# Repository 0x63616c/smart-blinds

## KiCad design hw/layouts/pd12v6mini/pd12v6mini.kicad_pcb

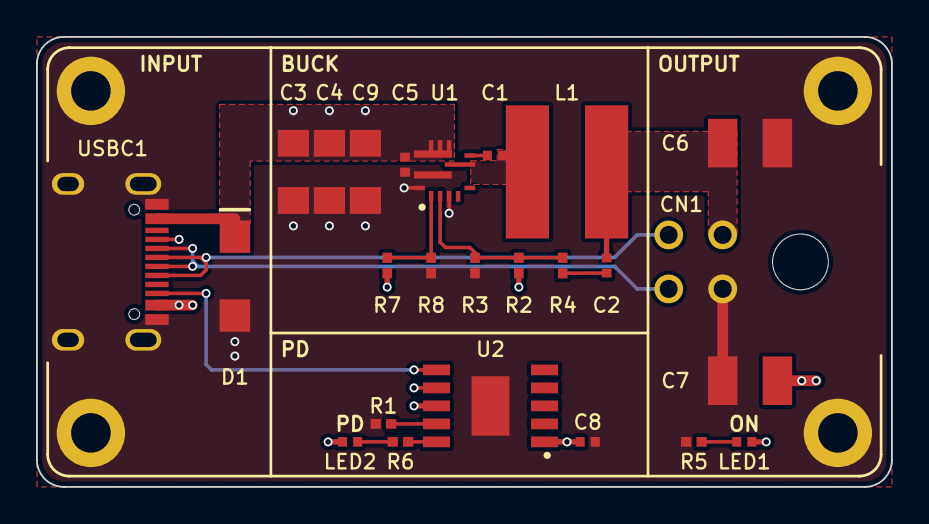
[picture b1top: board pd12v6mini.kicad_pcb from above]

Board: 4 copper layers, 47.5 x 25.0 mm, 29 parts (0 on the bottom side), 16 nets.

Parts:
C1, C2, C5, C8: C0402
C3, C4, C9: C1206
C6, C7: C1210
CN1: CONN-TH_0430450400
D1: SMA_L4.4-W2.6-LS5.0-RD
H1, H2, H3, H4: M2_HOLE
L1: IND-SMD_PSTMAA666460-6R8MB
LED1: LED0402-RD_GREEN
LED2: LED0402-RD
R1, R2, R3, R4, R5, R6, R7, R8: R0402
U1: VQFN-HR-10_L3.0-W3.0_RPA
U2: ESSOP-10_L4.9-W3.9-P1.0-LS6.0-TL-EP
USBC1: USB-C_SMD-TYPE-C-31-M-12_1

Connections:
BOOT: C1.1, U1.7
CC1: U2.7, USBC1.A5
CC2: U2.6, USBC1.B5
CFG1: R1.1, U2.9
EN: R7.2, R8.1, U1.1
FB: R2.2, R3.1, R4.2, U1.2
FF: C2.2, R4.1
GND: C3.2, C4.2, C5.2, C6.2, C7.2, C8.2, C9.2, CN1.2, D1.2, H1.1, H2.1, H3.1, H4.1, R1.2, R3.2, R5.2, R8.2, U1.3, U1.9, U1.10, U2.11, USBC1.1, USBC1.2, USBC1.3, USBC1.4, USBC1.A1B12, USBC1.B1A12
LED_OUT_K: LED1.1, R5.1
LED_PD_K: LED2.1, R6.1
PG_n: R6.2, U2.10
SW: C1.2, L1.1, U1.6
USB_DN: CN1.4, USBC1.A7, USBC1.B7
USB_DP: CN1.3, USBC1.A6, USBC1.B6
VBUS: C3.1, C4.1, C5.1, C8.1, C9.1, D1.1, LED2.2, R7.1, U1.8, U2.1, U2.8, USBC1.A4B9, USBC1.B4A9
VOUT: C2.1, C6.1, C7.1, CN1.1, L1.2, LED1.2, R2.1

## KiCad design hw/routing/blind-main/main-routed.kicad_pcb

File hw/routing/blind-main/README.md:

# Historical 196-part main-controller routing

This directory is the **historical 196-part routing checkpoint**, not the current
54 × 80 mm controller. Its source, geometry, manifests and validation results
belong together at [commit ea7bab1566812b4611e3c1e800e67b5ede44651c](https://github.com/0x63616c/smart-blinds/tree/ea7bab1566812b4611e3c1e800e67b5ede44651c).
That commit contains the exact source capture SHA
`2ef8c8d6168420d0de25bb6a4c4b3d778d73c1fd55e97ca068adafe70fbeadd7`
recorded in `route-record.json`. Reproduce its checks from that revision through
the isolated Linux runner. Do not point those checks at the newer 206-part
capture or present the historical findings as current-board validation.

This was a partial four-layer routing study, not a manufacturing release.
The derivative retains the 54 × 68.5 mm outline with its USB tab, all 196
footprints, 609 physical pin identities, 139 net partitions, 17 mechanical/thermal
anchors and 13 RF, connector-foot and clamp reservations.

The checkpoint contains 1013 segments and 255 vias. It routes the local charger
switching/bypass network, motor-driver fly/pump/VM and output paths, regulator
bypass/output/sense paths, and a 3.3 V feed to the radio module. In1 remains a
continuous filled ground-return island; no signal traces use that layer. The
module power feed uses In2 beneath the permitted module body, with vias outside
its solder lands and unchanged antenna keepouts.

Actual KiCad 10 DRC reports **122 unconnected items**. No short, copper/edge/hole
clearance, track-width, courtyard-overlap, keepout, mask-bridge or dangling-route
failure is accepted. The report retains 258 silkscreen/text findings, four
library-footprint differences and five footprint-type findings. The latter
include mixed through-hole/thermal features and incorrectly classified library
attributes; they require footprint/assembly review, not a blanket waiver.
Three unrelated default-disabled DRC categories are listed in `checks.json`.

`checks.py` independently checks actual pad shapes, masks/paste settings, net
partitions, layer/rotation/placement, outline, keepouts, courtyard bounds and
encoder-wire height clearance. It also follows physical copper shapes through
70 required connection groups, including the ground fill. A matching net name
alone cannot pass. Twenty-six earlier injected faults are rejected: moved USB connector, changed motor pad,
weakened RF reservation, cut module supply, removed return plane, cut charger
bypass return, cut PD bypass, cut USB input, removed quiet return via, and an
extra connection from the quiet return to the input-capacitor return, plus open
PD enable, UV divider, raw discharge and address-ground branches. The new controls
also cut the charger input, PMID and SYS bulk branches and input-capacitor return,
and place a same-net solder land over an ordinary open via. All 38 new distribution
vias preserve at least 0.20 mm from their drill edges to top solder lands; native
same-net clearance alone does not check this assembly condition. Both REGN and VBUS bypass
returns have two nearby ground vias, as required by the charger layout guide.
The checks remove the plane from the local graph before counting those vias. The generator is deterministic across repeated local runs.

The USB addition connects both VBUS contacts to the eFuse and its output
reservoir, with local input capacitance and a shunt TVS. It also connects the PD
supply diode and three separate bypass branches, and both CC/protection/dead-battery paths. The two MCU data resistors
have short local stubs; the completed data paths are described below. The eFuse's
current-setting, slew and divider-endpoint components return through an isolated
same-face branch to one ground via. An independent plane-free copper check
requires exactly those five quiet-ground pads and that one via; it rejects the
input-capacitor return joining this branch even though the net names agree.

The PNP enable stage, both voltage dividers, raw/output discharge chains and
PD address/reset/bus resistor branches are now connected. Their explicit
coordinates are replayed from `usb-control-routes.json`; reproduction performs
no route search. Five separate local ground vias serve the address and factory
bus resistors without joining the eFuse quiet-ground branch.

Factory access pads remain open; the USB data pair now reaches the module.
The completed control connections do not establish negotiated startup or
detach/discharge timing; the PD configuration and electrical tests remain
required. The 0.3 mm central-pad escapes and 0.8 mm back-layer power trunks
need current/temperature review; the present geometry is not a current rating.
The input TVS's specified pulse clamp can exceed downstream DC limits; placement
does not resolve that separate transient qualification issue. The eFuse layout
uses a quiet return, but loop impedance and coupling still need review.

The eFuse output now reaches the charger VBUS pins and input capacitors. The four
PMID and five SYS bulk capacitors connect to their existing local fast-bypass
branches through explicit two-via fanouts and In2 distribution traces. Input and
bulk-capacitor grounds join the uninterrupted In1 return. The replay coordinates
in `charger-power-banks.json` and `distribution.py` require no routing search.
The previous 581 copper items are retained. Fifteen previously unwired parts move
to make room, including the encoder supply block; all mechanical anchors remain.
These distributed reservoirs still need ripple-current, return-loop and thermal
review. The 0.6–0.8 mm In2 traces use 15.2 µm copper, so geometric clearance is not
a demonstrated continuous-current rating. Pack feed and onward SYS distribution
remain open.

The next extension connects both VAC inputs, BATP feedback, TS and ILIM networks,
PROG and their local returns. Six previously unwired control parts move; no
mechanical anchor changes. Its explicit paths in `charger-control-routes.json`
are replayed by `charger_controls.py`. A bootstrap via moves 0.25 mm to provide
two adjacent sensing escapes; its two incident traces follow it. The other 696
previous copper items are retained exactly. Seventeen control-area vias
(sixteen added and that relocated via) pass the same 0.20 mm drill-to-solder-land
margin, including same-net lands. Five new deliberate opens and a same-net
control-via intrusion are rejected. These connections need switch-noise,
feedback accuracy, thermal and transient review; full charger control, bus and
charge-permission wiring remain unfinished.

A subsequent assembly-clearance pass moves twelve ordinary vias by at most
0.35 mm and adjusts their sixteen incident traces. Five short top-layer stubs
preserve connections that previously relied on via copper touching a solder
land. No component moves. That earlier stage checked 178 routed vias. The clamp, USB and local supervision stages extend this to all 255 via drills, which remain at least 0.20 mm
from every top solder land, including lands on the same net; the ordinary
KiCad same-net clearance check alone does not ensure this. A deliberate
same-net intrusion at the USB input capacitor is rejected. The explicit
`via-land-clearance.json` changes replay through `via_lands.py`; this is not a
filled/capped via-in-pad process. Thermal holes inside library footprints still
require their separate solder/paste and assembly-process review.

The regenerative clamp now connects its eight-resistor bank, two series power
MOSFETs, detector/divider/feedback, local supply and bypasses, thermostat and latch.
Its 19 local multi-pad nets and eight load-path groups are checked using physical
copper, including every duplicate pad. Three separate plane-free return checks
keep the load, quiet detector and LDO bypass returns distinct before their plane
entries. Eight additional injected faults reject opens and an incorrect shared
return. All 34 old/new fault controls pass. The external `thermal_ok` and `G`
connections to the main inhibit and fault indication remain open.

`regen.py` consumes the preceding pipeline stage and replays finite geometry from
`regen-routes.json`; it does not embed a completed baseline or run a route search.
It replaces twelve exact low-current segments and one redundant NTC via, retains
all other incoming copper, and adds 249 items. Twenty-five previously unwired
clamp components move relative to the preceding published checkpoint. The eight
resistor and all mechanical anchors stay fixed. A now-obsolete NTC via is
explicitly required absent; the other sixteen control-area vias remain checked.

The selected 38.199 mm × 1.2 mm back-layer feed replaces an evaluated
48.804 mm × 0.8 mm detour. Nominal 35 µm-copper estimates at 20 °C are 15.68 mΩ
versus 30.05 mΩ, excluding vias, temperature and process variation. The actual
filled In1 plane contains a complete 1.2 mm swept-width, 39.802 mm return witness;
this is checked by polygon subtraction. It is not an ampacity or current-distribution
result. In1 is only 15.2 µm thick, and the eight 2 W resistor labels do not establish
16 W continuous capability for this compact assembly.

The shorter power loop requires three reviewed signal changes: PROG grows from
17.771 to 28.509 mm on B.Cu; NTC grows from 5.768 to 12.980 mm on B/F; the SW1 bootstrap
return shrinks from 8.087 to 4.175 mm. `regen_analog.py` reports their actual copper
neighbors and proves an intervening filled In1 shield at the NTC's projected
crossings with the B.Cu feed. The closest NTC segment remains only 0.205 mm from
the motor bulk PACK solder land; PROG remains a long startup-sampled branch.
These are explicit noise/layout qualification limits. A bounded 0.2 mm-grid search
for a closer one-part PROG relocation found no accepted closer position while
other parts/copper were fixed; it does not rule out a wider repack.

Comparator overshoot, FET SOA, pulse repetition, thermostat-to-resistor coupling,
printed-case/battery temperature and real motor regeneration remain untested.
An opened thermal cutoff cannot absorb sustained manual back-drive.

The complete placement change list is in `checks.json`. Many support components
have moved from the first placement to make local electrical loops possible.
The critical-loop review remains incomplete: especially charger bootstrap
routing, current/return geometry, switch-node coupling and module supply
impedance. The external 100 nF and bulk radio capacitors are about 18 mm from
the module supply pin; the wide internal feed is a layout candidate, not
proof of adequate local decoupling. Geometric clearance does not establish
electrical performance.

The USB data extension connects both reversible contact pairs through the moved
TPD2E2U06 and the existing module-side 22 Ω resistors. The ESD package moves to
local (22.8, 1.7), 180°; only its three old ground branches/two vias and three CC1
segments are replaced. `usb_data.py` consumes the current clamp output and
replays `usb-data-routes.json`. The base placement remains in `placement.json`;
that data file contains the explicit final ESD override. All other incoming
copper and the circuit graph remain unchanged, including after filling/saving.

Both long front traces have continuous direct In1 reference. A local In2 ground
zone references the short back crossover. The saved fill is checked for overlap
with each signal via, and missing reference is accepted only within D-minus's
own necessary via openings, with the project's 5 µm polygon-arc tolerance plus
0.5 µm audit tolerance. A prior saved merge had stale filled polygons; the
maintained stage now rebuilds and persists them. The neighboring D-plus segment
no longer clips D-minus's antipad. One short ESD pin-4 return reaches one local
via; optional NC pins 1/2 are grounded as TI permits.

The actual track-centerline graph gives approximately 88.235 mm from each A-side
contact to its series resistor and 89.235 mm from each B-side contact. It also
checks that each shortest path passes through its protection pad, and removing
that pad node must disconnect every connector-to-resistor centerline path. D-minus uses
two active through-layer transitions; D-plus uses none. Planar length equality
is **not** electrical-delay equality or a 90 Ω impedance result. One localized
D-plus fold at v23–24.8 replaces the earlier two-fold study and adds about
6.264 mm; the longer perimeter is parallel. The fold temporarily widens the pair
spacing, and the connector-side protection lead remains a layout tradeoff.
These need stackup/return-field/ESD review and actual full-speed USB tests.

Six new fault controls cut a D-plus branch, one D-minus reversible contact,
the ESD return, the back reference, and restore stale ground within a signal
antipad, and add a longer parallel path that bypasses the ESD pad.
All 40 controls through the USB stage pass; the later supervision stage brings the total to 47. The physical USB data connections are
complete; USB performance and manufacturing acceptance remain unfinished.

## Rules and outstanding work

The study retains the preliminary 1.6 mm JLC3313 four-layer descriptor: 35 µm
outer and 15.2 µm inner copper. Comparative minima are 0.15 mm trace/clearance,
0.20 mm copper-to-edge and hole-to-copper, 0.25 mm hole-to-hole, 0.20 mm minimum
hole and 0.10 mm annular ring. Ordinary route vias are 0.6/0.3 mm; selected
fine-pitch escapes use 0.5/0.25 mm. Existing thermal holes require their own
mask/paste/assembly-process review. These rules are not a current rating,
impedance approval, assembly quote or final fabrication profile.

Still unfinished: USB factory access and impedance/ESD qualification, pack feed and onward SYS
current distribution, clamp external inhibit/fault connections and onward supervisor buses, complete signal
routing, thermal and transient review, sparse silkscreen, final ERC/DRC and a
manufacturing quote. No autorouter result substitutes for the local power-layout review.

The [local supervision stage](local-supervision.md) adds 59 checked branches and
seven injected faults to the protected USB checkpoint. All 47 fault controls pass.
It preserves the incoming copper and moves fourteen previously unwired small
parts. The local encoder returns meet at the regulator GND land, checked by
physically cutting that land from the graph. Longer bypass/pull-up paths and the
unfinished ADC connection remain explicit layout limitations.

The [monitored-PD revision](../../../docs/electrical/monitored-pd-revision.md)
removes the obsolete VSYS-ground branch and two factory bus pull-downs from the
maintained stages. It preserves all1268 surviving copper items and all194 common
footprint placements. The two new parts are staged but unrouted; shared SDA/SCL,
ALERT and the new VSYS bypass still need physical routing. All47 existing fault
controls pass against the revised graph. No new feeder SKU is introduced.

## Reproduce

Use KiCad 10 and its distribution Python bindings, from the repository root:

```sh
xvfb-run -a /usr/bin/python3 hw/routing/blind-main/route.py
xvfb-run -a /usr/bin/python3 hw/routing/blind-main/checks.py --negative-tests
```

On macOS use KiCad's bundled Python, without `xvfb-run`. Intermediate files stay
under `work/main-route-build/`. The checked-in project template is used; no
untracked local KiCad project or global rule override is required. Never pass
this routed derivative through the unrouted-only atopile normalizer.

Layout references: [BQ25798, §8.4](https://www.ti.com/lit/ds/symlink/bq25798.pdf),
[DRV8874, §10](https://www.ti.com/lit/ds/symlink/drv8874.pdf),
[TPS62902, §8.5](https://www.ti.com/lit/ds/symlink/tps62902.pdf),
[Espressif layout guidance](https://docs.espressif.com/projects/esp-hardware-design-guidelines/en/latest/esp32c6/pcb-layout-design.html),
[official DevKit layout](https://dl.espressif.com/dl/schematics/esp32-c6-devkitc-1-pcb-layout_v1.2.pdf),
[STUSB4500](https://www.st.com/resource/en/datasheet/stusb4500.pdf),
[TPS25947, §8.4](https://www.ti.com/lit/ds/symlink/tps25947.pdf),
[TLV6710, §11](https://www.ti.com/lit/ds/symlink/tlv6710.pdf),
[TPS709, §10.1](https://www.ti.com/lit/ds/symlink/tps709.pdf),
[TMP302](https://www.ti.com/lit/ds/symlink/tmp302.pdf),
[JLC capabilities](https://jlcpcb.com/capabilities/pcb-capabilities), and
[JLC stackups](https://cart.jlcpcb.com/client/template/placeOrder/impedance.html).
These guide the study; they do not validate the finished board.

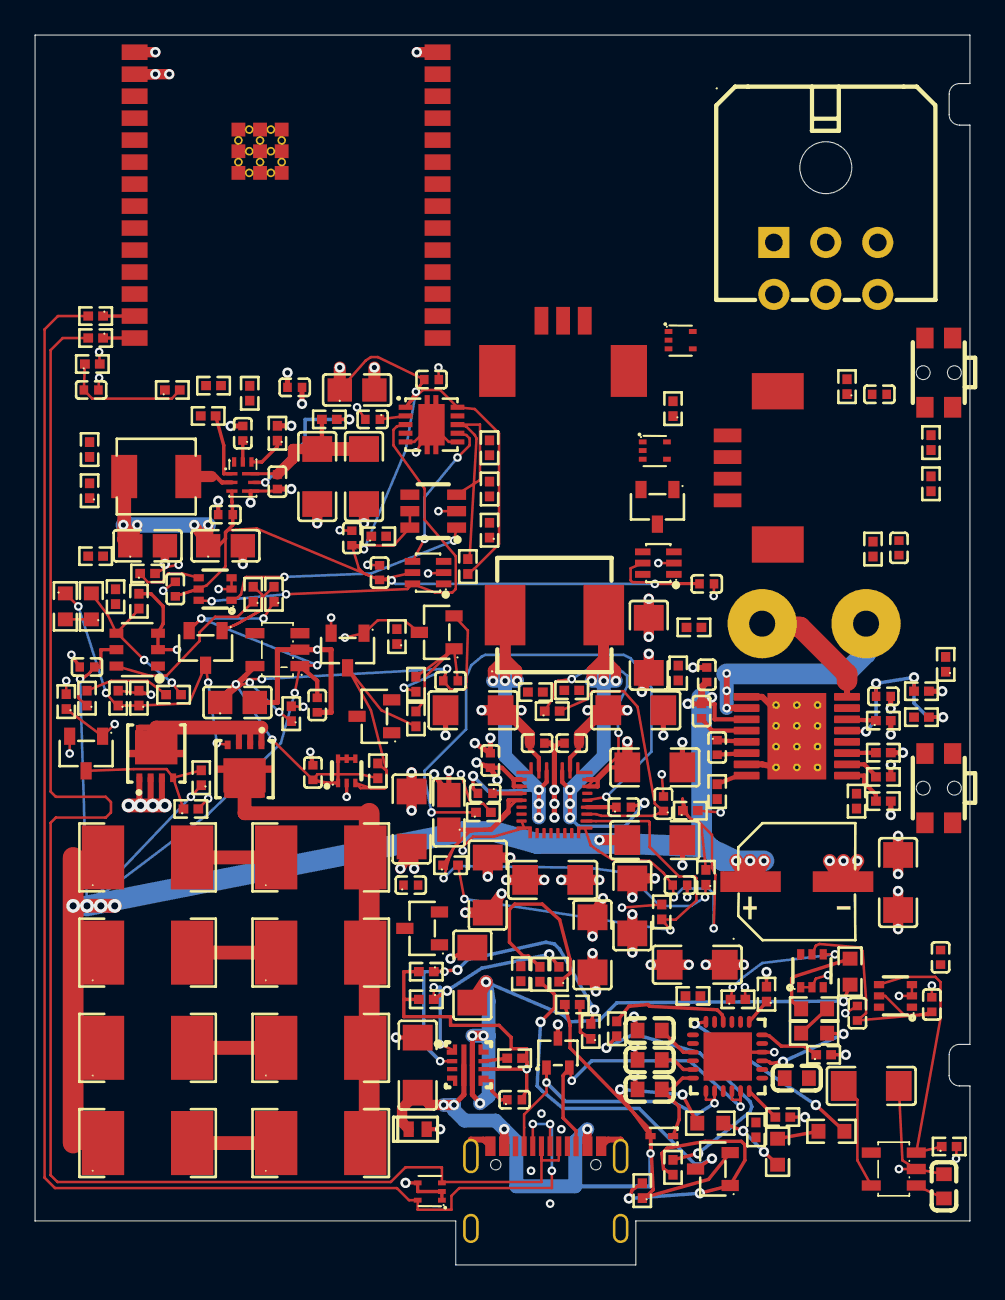
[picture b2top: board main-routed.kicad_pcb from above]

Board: 4 copper layers, 54.0 x 71.0 mm, 196 parts (0 on the bottom side), 110 nets.

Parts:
C1, C2, C6, C7, C9, C10, C11, C12, C16, C17, C18, C19, C20, C40, C42, C49, C54: C1206
C3, C4, C5, C8, C13, C15, C21, C22, C23, C24, C26, C27, C28, C29, C30, C32, C33, C34, C35, C36, C37, C38, C41, C45, C46, C50, C52, C55, C56, C57, C58, C59, C60: C0402
C14, C25, C39, C43, C44: C0805
C31: CAP-SMD_BD6.3-L6.6-W6.6-LS7.3-FD
C47, C48, C51, C53, C61: C0603
D1, D2, D6: SOT-553-5_L1.6-W1.2-P0.50-LS1.6-TL-1
D3: SOD-523_L1.2-W0.8-LS1.6-RD
D4: SOT-323-3_L2.1-W1.3-P1.32-LS2.1-BR
D5: DFN1610-2_L1.6-W1.0-P1.05-RD
J1: CONN-TH_43045-0600
J2: CONN-SMD_4P-P1.25_53261-0471
J3: CONN-TH_532610371
L1: IND-SMD_L7.2-W6.6_GPSR07X0
L2: IND-SMD_L4.4-W4.2
Q1, Q2, Q3, Q4, Q5, Q7, Q8, Q10: SOT-23-3_L2.9-W1.3-P1.90-LS2.4-BR
Q6, Q9: PDFN-8_L3.3-W3.3-P0.65-BL
R1, R2, R3, R4, R5, R6, R7, R8, R9, R10, R11, R12, R13, R14, R15, R16, R17, R18, R19, R20, R21, R22, R23, R24, R25, R26, R27, R28, R29, R30, R31, R32, R33, R34, R35, R36, R37, R38, R39, R40, R41, R44, R45, R46, R47, R48, R49, R50, R51, R52, R56, R57, R58, R62, R63, R65, R66, R67, R68, R77, R78, R79, R80, R81, R82, R83, R84, R85, R86, R87, R88, R89, R90, R91, R92, R93: R0402
R42, R43, R69, R70, R71, R72, R73, R74: R2512
R53, R54, R55, R59, R60, R61, R75, R76: R0603
SW1, SW2: SW-SMD_4P-L3.5-W3.0-P1.6-LS4.6
TP1, TP2: WirePad18
U1: QFN-29_L4.0-W4.0-P0.40-TL-BQ25792RQMR
U2, U14: SOT-363_L2.0-W1.3-P0.65-LS2.1-BR
U3: WIRELM-SMD_ESP32-C6-WROOM-1
U4: HTSSOP-16_L5.0-W4.4-P0.65-LS6.4-BL-EP
U5: TSOT-23-6_L2.9-W1.6-P0.95-LS2.8-BR
U6, U13: SOT-23-5_L3.0-W1.7-P0.95-LS2.8-BR
U7: SOT-5X3-6_W1.6-L1.2-P0.50-LS1.6-BL
U8, U12, U17: SC-70-6_L2.0-W1.3-P0.65-LS2.1-BR
U9: VQFN-HR-9_L2.0-W1.5-P0.50-TL
U10: VQFN-10_L2.0-W2.0-P0.45-TL
U11: QFN-24_L4.0-W4.0-P0.50-BL-EP2.8
U15: SOT-23-6_L2.9-W1.6-P0.95-LS2.8-BR
U16: VSON-10_L3.0-W3.0-P0.50-TL-EP
USBC1: HRO_TYPE_C_31_M_12

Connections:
1: C4.1, U1.4
2: C5.2, L1.2, U1.26
4: U2.4, U3.7
6: U2.6, U3.6
10: R29.2, U3.10
ALERT: R63.2, U1.21, U3.24, U11.19
BATP: C3.1, R1.2, U1.18
C: Q3.3, R66.1
CC2: D4.2, U11.4, U11.5, USBC1.B5
CE_n: Q1.3, R2.2, U1.13
CPH: C32.1, U4.13
CPL: C32.2, U4.14
CWD: C59.1, U16.2
D: Q10.3, R32.2, U3.19, U4.4
DISCH: R55.2, U11.9
DVDT: C50.1, U10.7
EN: R68.1, U12.4, U13.3
G: Q4.1, Q7.1, Q8.3, Q10.1, R88.1
ILIM_HIZ: R4.1, R5.2, U1.17
ILM: R52.1, U10.9
MODE_S_CONF: R45.1, U9.7
MR: R93.2, U15.3, U16.8
OUTB: R40.1, U5.6
PG: R46.2, U9.1
PMODE: R35.2, U4.16
PROG: R8.1, U1.20
RESET: R62.1, U11.6
SCL: J1.4, R27.2, U1.14, U3.12, U11.7
SDA: J1.3, R28.2, U1.15, U3.11, U11.8
SDRV: C15.1, U1.24
SS_TR: C46.1, U9.8
SW: L2.1, U9.2
VBUS_EN_SNK: R50.2, U11.16
VBUS_VS_DISCH: R61.2, U11.18
VCP: C33.1, U4.12
WDI: U14.4, U16.7
Y: R38.1, R39.1, U4.3, U17.4
allow_n-line: R24.2, U3.21, U12.6
boot_n: R19.2, U3.15
c_1v2-1: C47.1, U11.21
c_2v7-1: C48.1, U11.23
c_adc-1: C24.1, R14.2, R15.1, U3.27
c_boot1-1: C4.2, L1.1, U1.28
c_boot2-1: C5.1, U1.19
c_down-1: C27.1, R22.2, SW1.1, SW1.2, U3.9
c_hot_filter-1: C37.1, C39.1, C55.1, Q8.2, R80.1, R81.1, R83.1, U6.5, U7.1, U7.4, U7.5, U7.6
c_pmid1-1: C9.1, C10.1, C11.1, C12.1, C13.1, U1.29
c_ref-1: C34.1, R36.2, R37.1, U4.5
c_regn-1: C14.1, R2.1, R5.1, R10.1, U1.5
c_up-1: C30.1, R30.2, SW2.1, SW2.2, U3.8
c_vdd-1: C51.1, D3.1, U11.24
channel_a: D1.3, J2.3, R12.1, R13.2
channel_b: D1.5, J2.4, R17.1, R18.2
charger-1: Q1.1, Q2.3, R3.1
charger-1-1: Q2.1, R6.2, R7.1
connector-1: D4.1, U11.1, U11.2, USBC1.A5
controller-1: R11.1, R12.2, U2.1
controller-1-1: R16.1, R17.2, U2.3
controller-1-2: R21.1, U3.13
controller-1-3: R23.1, U3.14
controller-2: C29.1, R25.2, R26.2, U3.26
current_raw: R14.1, R31.1, U4.6
efuse-1: R65.1, R67.2, U10.1
encoder-output-hv: C54.1, J2.2, R13.1, R18.1, U13.5
heartbeat-line: R92.2, U3.25, U14.3
home_contact_n: D6.3, D6.5, J3.3, R25.1
host_logic-hv: C23.1, C25.1, C26.1, C28.1, C43.1, C44.1, C45.1, C52.1, C56.1, C57.1, C58.1, C60.1, C61.1, L2.2, Q2.2, R7.2, R19.1, R20.1, R22.1, R24.1, R26.1, R27.1, R28.1, R29.1, R30.1, R32.1, R35.1, R36.1, R46.1, R63.1, R89.1, R90.1, R92.1, R93.1, U2.5, U3.2, U8.5, U9.3, U11.22, U12.5, U14.5, U15.5, U15.6, U16.1, U16.10, U17.5
hv: C1.1, C2.1, C31.1, C33.2, C35.1, C36.1, C38.1, J1.1, Q5.2, R1.1, R41.1, R42.1, R69.1, R71.1, R73.1, R84.1, R86.1, U1.22, U1.23, U4.11, U5.5, U6.1
in1-1: R33.1, U3.16, U4.1
in2-line: R34.1, U3.17, U4.2
line: R6.1, R20.2, U3.20
logic_supply-EN: R44.2, U9.5
lv: C1.2, C2.2, C3.2, C6.2, C7.2, C8.2, C9.2, C10.2, C11.2, C12.2, C13.2, C14.2, C15.2, C16.2, C17.2, C18.2, C19.2, C20.2, C21.2, C22.2, C23.2, C24.2, C25.2, C26.2, C27.2, C28.2, C29.2, C30.2, C31.2, C34.2, C35.2, C36.2, C38.2, C39.2, C40.2, C41.2, C42.2, C43.2, C44.2, C45.2, C46.2, C47.2, C48.2, C49.2, C50.2, C51.2, C52.2, C53.2, C54.2, C55.2, C56.2, C57.2, C58.2, C59.2, C60.2, C61.2, D1.1, D1.2, D1.4, D2.1, D2.2, D2.4, D4.3, D5.2, D6.1, D6.2, D6.4, J1.2, J1.6, J2.1, J3.1, Q1.2, Q4.2, Q7.2, Q9.1, Q9.2, Q9.3, Q10.2, R3.2, R4.2, R8.2, R9.2, R11.2, R15.2, R16.2, R31.2, R33.2, R34.2, R37.2, R38.2, R39.2, R45.2, R47.2, R48.2, R52.2, R56.2, R62.2, R65.2, R68.2, R77.2, R78.2, R81.2, R82.2, R85.2, R88.2, R91.2, SW1.3, SW1.4, SW2.3, SW2.4, U1.10, U1.11, U1.27, U2.2, U3.1, U3.28, U3.29, U3.30, U3.31, U3.32, U3.33, U3.34, U3.35, U3.36, U3.37, U4.9, U4.15, U4.17, U5.2, U5.3, U6.2, U7.2, U8.2, U8.3, U9.4, U10.8, U11.10, U11.25, U12.2, U12.3, U13.2, U14.2, U15.2, U16.5, U16.6, U16.11, U17.1, U17.2, USBC1.1, USBC1.2, USBC1.3, USBC1.4, USBC1.A1B12, USBC1.B1A12
motor_a: TP1.1, U4.8
motor_b: TP2.1, U4.10
motor_request_n-line: R89.2, U3.18, U14.1
motor_sleep_n-Y: R91.1, U8.4, U17.3
pack_ntc: C22.1, J1.5, R9.1, R10.2, U1.16
pd-1: R47.1, U11.12
pd-1-1: R48.1, U11.13
q_drive-1: Q5.3, Q6.4, R75.1, R77.1, R78.1
q_enable-1: Q3.1, R49.1, R51.2
r_base1-1: R49.2, R50.1
r_dump1a-1: R42.2, R43.1
r_dump2a-1: R69.2, R70.1
r_dump3a-1: R71.2, R72.1
r_dump4a-1: R73.2, R74.1
r_feedback1-1: R75.2, R76.1
r_out_dis1-1: R53.2, R54.1
r_out_dis2-1: R54.2, R55.1
r_ov_top1-1: R57.2, R58.1
r_raw_dis1-1: R59.2, R60.1
r_raw_dis2-1: R60.2, R61.1
r_threshold_top1-1: R86.2, R87.1
r_uv_top1-1: R66.2, R67.1
raw-hv: C49.1, D3.2, D5.1, Q3.2, R51.1, R57.1, R59.1, U10.5, USBC1.A4B9, USBC1.B4A9
regen-2: C37.2, Q8.1, R79.2, R80.2
regen-2-1: Q6.5, Q6.6, Q6.7, Q6.8, Q6.9, R43.2, R70.2, R72.2, R74.2
regen-2-2: Q5.1, R40.2, R41.2
reset_n: R90.2, U3.3, U8.1, U12.1, U15.1
series_mid: Q6.1, Q6.2, Q6.3, Q9.5, Q9.6, Q9.7, Q9.8, Q9.9
source-hv: C16.1, C17.1, C18.1, C19.1, C20.1, C21.1, C40.1, C41.1, C42.1, C53.1, R44.1, U1.25, U9.6, U13.1
supervision-6: U8.6, U14.6, U16.3
thermal_gate: Q4.3, Q9.4, R82.1, R84.2
thermal_ok: Q7.3, R79.1, R83.2, U7.3, U17.6
threshold: R76.2, R85.1, R87.2, U5.4
usb-2: R56.1, R58.2, U10.2
usb-output-hv: C6.1, C7.1, C8.1, R53.1, U1.2, U1.3, U1.8, U1.9, U10.6
usb_dm: D2.5, R21.2, USBC1.A7, USBC1.B7
usb_dp: D2.3, R23.2, USBC1.A6, USBC1.B6

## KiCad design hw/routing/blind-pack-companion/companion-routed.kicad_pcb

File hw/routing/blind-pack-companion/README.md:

# Experimental companion-carrier route

This is a connected **two-layer routing experiment**, not a fabrication release.
The original carrier under `hw/layouts/blind-pack-companion/` remains the
atopile circuit and placement authority. The routed copy uses native KiCad 10,
35 copper segments, 12 vias, and no copper pours.

Red is outward-face copper; blue is inward-face copper. The companion view is
mirrored horizontally relative to the shared assembly coordinates.

The latest actual KiCad DRC has **zero unconnected items** and no copper,
hole, edge, short, courtyard-overlap or keepout failures. The
[routed-project footprint cleanup](../carrier-finish/README.md) removes the six
fuse/holder silkscreen findings without changing pads, connections or polarity
marks. Matching local libraries also pass native footprint-library comparison.
Enabling KiCad's normally disabled missing-courtyard check reports
four errors on the board-only NPTH mounting holes H1–H4. Those exact mechanical
features are retained and reported; all ten purchased-component courtyards are
present and independently checked. The footprint-type check is also explicitly
enabled and passes. No exclusions or waivers were added. `drc.json` retains the
complete report; this is not a zero-error fabrication result.

All severities are requested, but that does not enable disabled categories.
Three unrelated KiCad defaults remain disabled: symbol footprint-filter
matching (no paired native schematic in this derivative), track endpoint
centering on vias, and tuning-profile track geometry. The actual via geometry
and current transitions have separate checks. These defaults are listed in
`checks.json`; none is represented as a passed check.

Only three component placements differ: each nonpolar fuse is rotated 180°,
putting its unfused terminal toward the holder. All physical pin/net identities,
holder positions, mounting holes, outline, wire pads and component sides match
the canonical board. Item UUIDs are made unique so DRC reports identify the
correct physical instances; this does not change copper. New route items are
sorted by their geometry before stable UUID assignment, avoiding KiCad's random
creation-order serialization. Repeated generator runs produce byte-identical
PCB and project files.

The companion's upper support originally prohibited copper on both faces.
The coordinated enclosure change provides a 0.3 mm spacer recess for covered
B.Cu tracks inside local X=9–77, Y=94–97 mm. F.Cu stays bare. Pads, vias, lead
tails, mask openings and copper pours remain forbidden in this window; corner
supports, edge supports and RF restrictions remain intact. The separate
insulating barrier stays in place. Printed fit, tolerance and insulation wear
still need physical qualification.

Long current routes are 3 mm wide; short fanout and unfused links are 2 mm.
The provisional construction is 1.6 mm FR-4 with 1 oz outer copper. Via lands
are 0.9 mm with 0.4 mm finished holes, four per fused branch, tented on both
faces. Every via drill clears every top SMD solder land by at least 0.20 mm,
including same-net lands; an intentional same-net intrusion is rejected. The project rules require 0.25 mm
copper clearance and 0.30 mm edge clearance. These choices fit within the
[JLC capability table](https://jlcpcb.com/capabilities/pcb-capabilities); they
are not a 4 A current or thermal qualification.

From the actual route dimensions, the nominal copper-only loss is about
**0.242 W / 0.121 V** when each companion cell carries 2 A. That assumes equal
sharing with the primary cells and no current in the middle inter-board links.
The 70°C / 20% narrower-track sensitivity gives 0.351 W in the traces alone.
`copper-losses.json` also evaluates unequal and missing-cell cases; it excludes
cells, holders, fuses, solder, inter-board wires, the primary shunt/FETs and
connectors. A 4 A individual branch is a fault/transient planning case, not
approved continuous operation through a 3 A fuse or an unrated holder.

`checks.py` compares actual footprint pads and electrical identities, mounting
features, outline, all retained support/RF areas, reviewed courtyard envelopes,
unique UUIDs and the exact covered-track exception. It also rejects mask
openings in the protected region. Five fault controls move a same-net via into a fuse land, remove a real current
rail, permit a via in the recessed support strip, add a solder-mask opening,
and misattribute a missing-courtyard finding to a purchased component.
The removed rail is rejected by an actual KiCad DRC run, not merely a source
netlist comparison.

Reproduce with KiCad's Python runtime:

```sh
/Applications/KiCad.app/Contents/Frameworks/Python.framework/Versions/3.9/bin/python3.9 hw/routing/blind-pack-companion/route.py
/Applications/KiCad.app/Contents/Frameworks/Python.framework/Versions/3.9/bin/python3.9 hw/routing/blind-pack-companion/checks.py --negative-tests
python3 hw/routing/blind-pack-companion/estimate_losses.py
```

On Linux with KiCad 10 and its distribution Python packages, use
`xvfb-run -a /usr/bin/python3 hw/routing/blind-pack-companion/checks.py --negative-tests`.
Use the same interpreter for `route.py`; the generic setup-python environment
does not supply KiCad's `pcbnew`/`wx` bindings.

Do not pass the routed copy through the canonical placement normalizer, hole
restorer or atopile build. Those tools intentionally own unrouted circuit
captures. `route-record.json` and `checks.json` record the exact source and
mechanical hashes for this experiment.

Remaining work includes fabrication/assembly review,
controlled pack commissioning, holder/contact heating, fuse interruption,
cell matching/reverse insertion, failed-short protection, retained flexible
raw links and insertion-fixture qualification. No manufacturing outputs or
purchase have been produced.

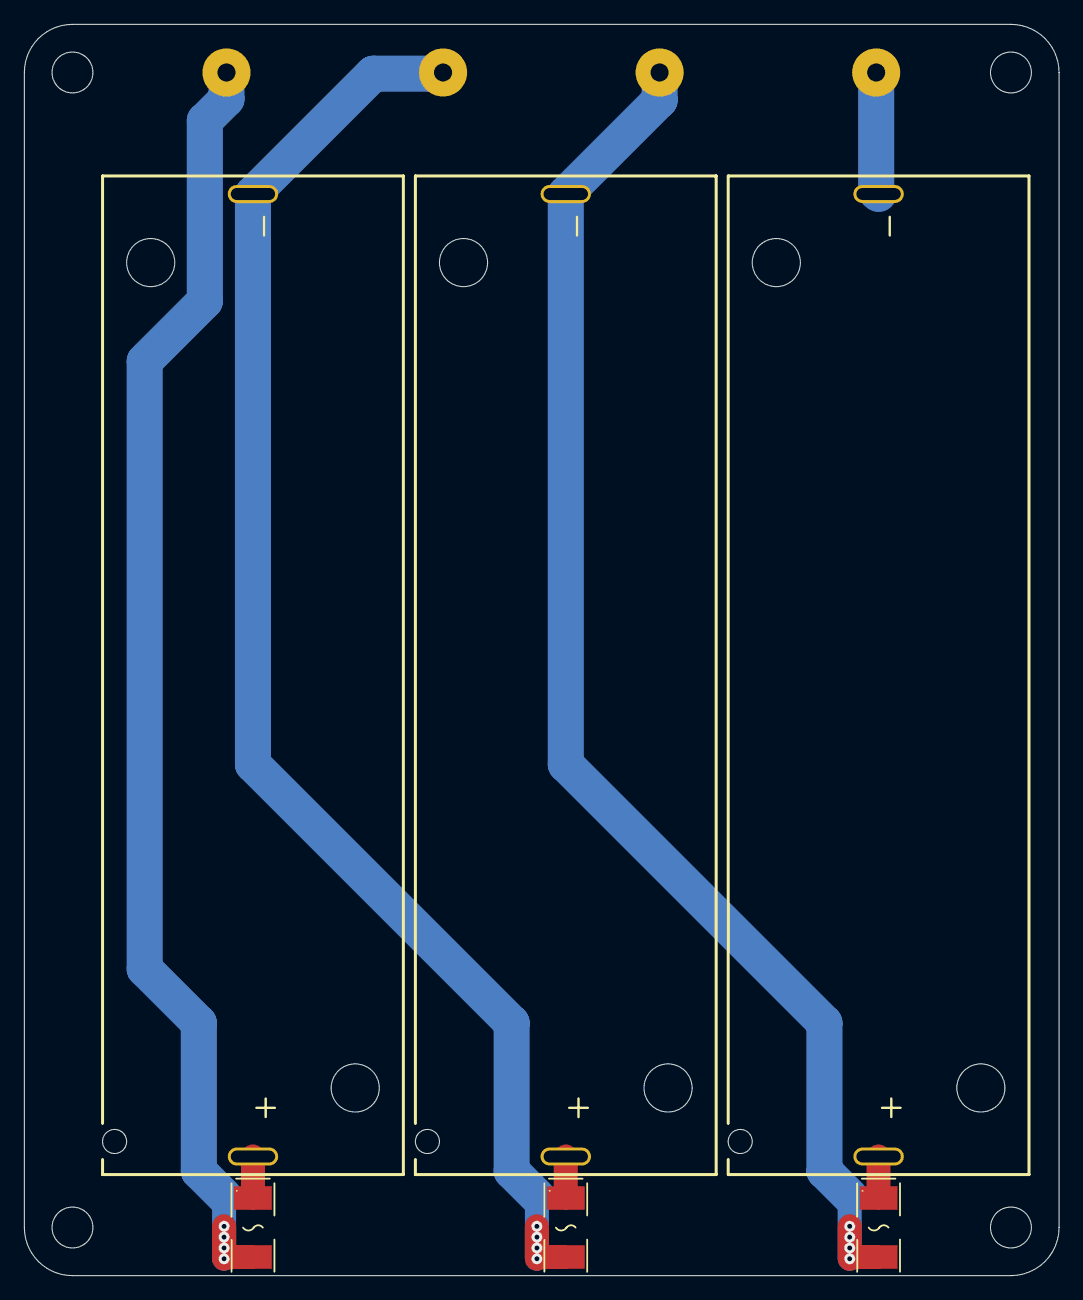
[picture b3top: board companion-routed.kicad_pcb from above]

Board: 2 copper layers, 86.0 x 104.0 mm, 14 parts (0 on the bottom side), 7 nets.

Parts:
BT1, BT2, BT3: BAT-TH_BH-21700-A5BJ001
F1, F2, F3: FUSE-SMD_L6.1-W2.7
H1, H2, H3, H4: M3 clearance 3.4 mm; MountingHole_M3_3.4mm
TP1, TP2, TP3, TP4: WirePad18

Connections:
1: BT1.1, F1.1
2: BT2.2, F1.2, TP1.1
carrier-1: BT2.1, F2.1
carrier-1-1: BT3.1, F3.1
carrier-2: BT3.2, F2.2, TP2.1
raw_ground: BT1.2, TP3.1
raw_top: F3.2, TP4.1
